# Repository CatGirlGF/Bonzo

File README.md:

# Bonzo
## Pro Micro based custom pseudo 40% keyboard inspired by [V4N4G0N](https://trashman.wiki/keyboards/v4n4g0n)

## Kicad libraries used:

https://github.com/AcheronProject/AlexandriaLibrary
https://github.com/keebio/Keebio-Parts.pretty
https://github.com/ai03-2725/MX_Alps_Hybrid/tree/master/MX_Only.pretty

## Gerbers

The provided gerbers have been created according to the specifications of JLCpcb. For plate the size is 275.3mm * 113.4mm

## Cases 

### Acryllic case

The case is designed to be cut out of 3mm acryllic and uses a 1.5mm switchplate.

I used 4mm female to female M2 standoffs from this listing: https://www.aliexpress.com/item/1005003106030065.html

https://i.imgur.com/W8KVRhH.png Picture for reference if the listing gets deleted

### 3D printable case WIP

This case has been printed fully and works, but the screwholes are too tight and have to be drilled.

Updated case design with heat insrets and correct size holes at some point.

## Firmware 

I have provided a compiled .hex and a layout json that will let you use the keyboard with VIA.

The full QMK library is also provided incase it is needed.

## BOM

### General parts for wired

| Name                    | Pieces | Description                          |
| ----------------------- | ------ | ------------------------------------ |
| PCB                     | 1      | Gerbers available at this repository |
| 1,5mm switch plate      | 1      | Gerbers available at this repository |
| 2U PCB mount stabilizer | 3      | Also known as screw-in stabilizers   |
| MX hotswap sockets      | 54     | Kailh or equivalent                  |
| MX style switch         | 54     |                                      |
| 1N4148 diodes           | 54     | SOD-123 packaging                    |
| ProMicro or similar     | 1      |                                      |

### For Wireless

| Name                    | Pieces | Description                                                                                            |
| ----------------------- | ------ | ------------------------------------------------------------------------------------------------------ |
| PCB                     | 1      | Gerbers available at this repository                                                                   |
| 1,5mm switch plate      | 1      | Gerbers available at this repository                                                                   |
| 2U PCB mount stabilizer | 3      |                                                                                                        |
| MX hotswap sockets      | 54     | Kailh or equivalent                                                                                    |
| MX style switch         | 54     |                                                                                                        |
| 1N4148 diodes           | 54     | SOD-123 packaging                                                                                      |
| nice!nano v2            | 1      |                                                                                                        |
| LiPo battery            | 1      | Refer to [nice!nano's documentation](https://nicekeyboards.com/docs/nice-nano/) on battery suggestions |
| Slide switch            | 1      | JS202011AQN or similar                                                                                 |

#### For acryllic case

| Name                               | Pieces    | Description                        |
| ---------------------------------- | --------- | ---------------------------------- |
| Acrylic layers                     | 1 of each | Files available in this repository |
| 4-6mm M2 female - female standoffs | 8         | Hexagon shaped ones won't fit      |
| M2 screws                          | 16        |                                    |

#### For 3DP case

| Name         | Pieces | Description                         |
| ------------ | ------ | ----------------------------------- |
| Top case     | 1      |                                     |
| Bottom case  | 1      |                                     |
| M2x15 screws | 4      | Self-tapping screws are recommended |
| M2x10 screws | 4      | Self-tapping screws are recommended |

## Keycaps
You will also need keycaps to fit the layout pictured below 

# Disclaimer
**Everything in this repo has been published with intent to allow others to build this keyboard if they want to and is published under MIT License. The versions I have uploaded have been tested to work. I take no responsibility of designs being incorrect or flawed. Check all the files yourself before you purchase anything. If something is broken or missing please let me know and ill try and see if I can fix the issue.**

Also here is the cat who inspired the name and the silkscreen

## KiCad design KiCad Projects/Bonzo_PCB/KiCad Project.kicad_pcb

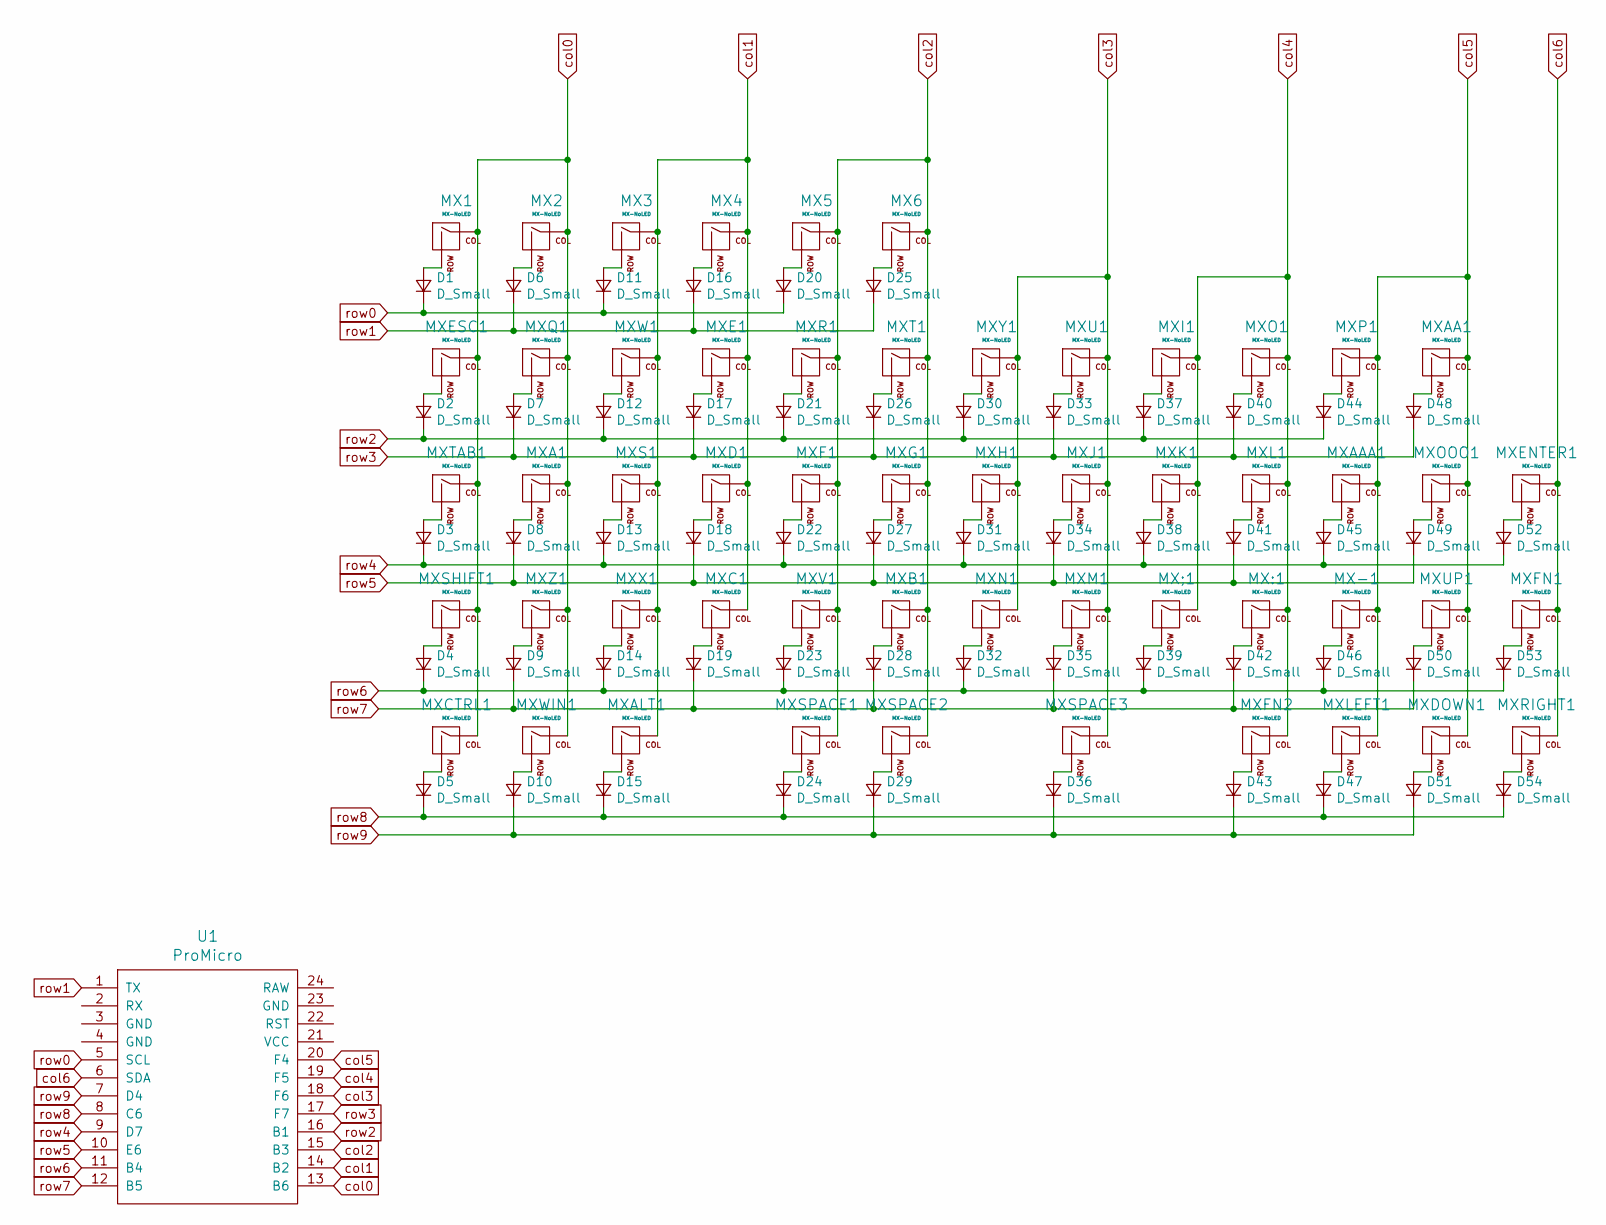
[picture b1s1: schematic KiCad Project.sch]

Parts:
D1, D2, D3, D4, D5, D6, D7, D8, D9, D10, D11, D12, D13, D14, D15, D16, D17, D18, D19, D20, D21, D22, D23, D24, D25, D26, D27, D28, D29, D30, D31, D32, D33, D34, D35, D36, D37, D38, D39, D40, D41, D42, D43, D44, D45, D46, D47, D48, D49, D50, D51, D52, D53, D54: D_Small; D_SOD123
MX1, MX2, MX3, MX4, MX5, MX6: MX-NoLED; MXOnly-1U-Hotswap
MX-1: MX-NoLED; MXOnly-1U-Hotswap
MX:1: MX-NoLED; MXOnly-1U-Hotswap
MX;1: MX-NoLED; MXOnly-1U-Hotswap
MXA1: MX-NoLED; MXOnly-1U-Hotswap
MXAA1: MX-NoLED; MXOnly-1U-Hotswap
MXAAA1: MX-NoLED; MXOnly-1U-Hotswap
MXALT1: MX-NoLED; MXOnly-1.25U-Hotswap
MXB1: MX-NoLED; MXOnly-1U-Hotswap
MXC1: MX-NoLED; MXOnly-1U-Hotswap
MXCTRL1: MX-NoLED; MXOnly-1.25U-Hotswap
MXD1: MX-NoLED; MXOnly-1U-Hotswap
MXDOWN1: MX-NoLED; MXOnly-1U-Hotswap
MXE1: MX-NoLED; MXOnly-1U-Hotswap
MXENTER1: MX-NoLED; MX_ISOEnter_VerticalH
MXESC1: MX-NoLED; MXOnly-1U-Hotswap
MXF1: MX-NoLED; MXOnly-1U-Hotswap
MXFN1, MXFN2: MX-NoLED; MXOnly-1U-Hotswap
MXG1: MX-NoLED; MXOnly-1U-Hotswap
MXH1: MX-NoLED; MXOnly-1U-Hotswap
MXI1: MX-NoLED; MXOnly-1U-Hotswap
MXJ1: MX-NoLED; MXOnly-1U-Hotswap
MXK1: MX-NoLED; MXOnly-1U-Hotswap
MXL1: MX-NoLED; MXOnly-1U-Hotswap
MXLEFT1: MX-NoLED; MXOnly-1U-Hotswap
MXM1: MX-NoLED; MXOnly-1U-Hotswap
MXN1: MX-NoLED; MXOnly-1U-Hotswap
MXO1: MX-NoLED; MXOnly-1U-Hotswap
MXOOO1: MX-NoLED; MXOnly-1U-Hotswap
MXP1: MX-NoLED; MXOnly-1U-Hotswap
MXQ1: MX-NoLED; MXOnly-1U-Hotswap
MXR1: MX-NoLED; MXOnly-1U-Hotswap
MXRIGHT1: MX-NoLED; MXOnly-1U-Hotswap
MXS1: MX-NoLED; MXOnly-1U-Hotswap
MXSHIFT1: MX-NoLED; MXOnly-1.5U-Hotswap
MXSPACE1: MX-NoLED; MXOnly-2.75U-Hotswap-ReversedStabilizers
MXSPACE2: MX-NoLED; MXOnly-1U-Hotswap
MXSPACE3: MX-NoLED; MXOnly-2.25U-Hotswap-ReversedStabilizers
MXT1: MX-NoLED; MXOnly-1U-Hotswap
MXTAB1: MX-NoLED; MXOnly-1.25U-Hotswap
MXU1: MX-NoLED; MXOnly-1U-Hotswap
MXUP1: MX-NoLED; MXOnly-1U-Hotswap
MXV1: MX-NoLED; MXOnly-1U-Hotswap
MXW1: MX-NoLED; MXOnly-1U-Hotswap
MXWIN1: MX-NoLED; MXOnly-1U-Hotswap
MXX1: MX-NoLED; MXOnly-1U-Hotswap
MXY1: MX-NoLED; MXOnly-1U-Hotswap
MXZ1: MX-NoLED; MXOnly-1U-Hotswap
U1: ProMicro; ArduinoProMicro

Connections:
unnamed: D1.2 (A), MX1.2 (ROW)
unnamed: D2.2 (A), MXESC1.2 (ROW)
unnamed: D3.2 (A), MXTAB1.2 (ROW)
unnamed: D4.2 (A), MXSHIFT1.2 (ROW)
unnamed: D5.2 (A), MXCTRL1.2 (ROW)
unnamed: D6.2 (A), MX2.2 (ROW)
unnamed: D7.2 (A), MXQ1.2 (ROW)
unnamed: D8.2 (A), MXA1.2 (ROW)
unnamed: D9.2 (A), MXZ1.2 (ROW)
unnamed: D10.2 (A), MXWIN1.2 (ROW)
unnamed: D11.2 (A), MX3.2 (ROW)
unnamed: D12.2 (A), MXW1.2 (ROW)
unnamed: D13.2 (A), MXS1.2 (ROW)
unnamed: D14.2 (A), MXX1.2 (ROW)
unnamed: D15.2 (A), MXALT1.2 (ROW)
unnamed: D16.2 (A), MX4.2 (ROW)
unnamed: D17.2 (A), MXE1.2 (ROW)
unnamed: D18.2 (A), MXD1.2 (ROW)
unnamed: D19.2 (A), MXC1.2 (ROW)
unnamed: D20.2 (A), MX5.2 (ROW)
unnamed: D21.2 (A), MXR1.2 (ROW)
unnamed: D22.2 (A), MXF1.2 (ROW)
unnamed: D23.2 (A), MXV1.2 (ROW)
unnamed: D24.2 (A), MXSPACE1.2 (ROW)
unnamed: D25.2 (A), MX6.2 (ROW)
unnamed: D26.2 (A), MXT1.2 (ROW)
unnamed: D27.2 (A), MXG1.2 (ROW)
unnamed: D28.2 (A), MXB1.2 (ROW)
unnamed: D29.2 (A), MXSPACE2.2 (ROW)
unnamed: D30.2 (A), MXY1.2 (ROW)
unnamed: D31.2 (A), MXH1.2 (ROW)
unnamed: D32.2 (A), MXN1.2 (ROW)
unnamed: D33.2 (A), MXU1.2 (ROW)
unnamed: D34.2 (A), MXJ1.2 (ROW)
unnamed: D35.2 (A), MXM1.2 (ROW)
unnamed: D36.2 (A), MXSPACE3.2 (ROW)
unnamed: D37.2 (A), MXI1.2 (ROW)
unnamed: D38.2 (A), MXK1.2 (ROW)
unnamed: D39.2 (A), MX;1.2 (ROW)
unnamed: D40.2 (A), MXO1.2 (ROW)
unnamed: D41.2 (A), MXL1.2 (ROW)
unnamed: D42.2 (A), MX:1.2 (ROW)
unnamed: D43.2 (A), MXFN2.2 (ROW)
unnamed: D44.2 (A), MXP1.2 (ROW)
unnamed: D45.2 (A), MXAAA1.2 (ROW)
unnamed: D46.2 (A), MX-1.2 (ROW)
unnamed: D47.2 (A), MXLEFT1.2 (ROW)
unnamed: D48.2 (A), MXAA1.2 (ROW)
unnamed: D49.2 (A), MXOOO1.2 (ROW)
unnamed: D50.2 (A), MXUP1.2 (ROW)
unnamed: D51.2 (A), MXDOWN1.2 (ROW)
unnamed: D52.2 (A), MXENTER1.2 (ROW)
unnamed: D53.2 (A), MXFN1.2 (ROW)
unnamed: D54.2 (A), MXRIGHT1.2 (ROW)
col0: MX1.1 (COL), MX2.1 (COL), MXA1.1 (COL), MXCTRL1.1 (COL), MXESC1.1 (COL), MXQ1.1 (COL), MXSHIFT1.1 (COL), MXTAB1.1 (COL), MXWIN1.1 (COL), MXZ1.1 (COL), U1.13 (B6)
col1: MX3.1 (COL), MX4.1 (COL), MXALT1.1 (COL), MXC1.1 (COL), MXD1.1 (COL), MXE1.1 (COL), MXS1.1 (COL), MXW1.1 (COL), MXX1.1 (COL), U1.14 (B2)
col2: MX5.1 (COL), MX6.1 (COL), MXB1.1 (COL), MXF1.1 (COL), MXG1.1 (COL), MXR1.1 (COL), MXSPACE1.1 (COL), MXSPACE2.1 (COL), MXT1.1 (COL), MXV1.1 (COL), U1.15 (B3)
col3: MXH1.1 (COL), MXJ1.1 (COL), MXM1.1 (COL), MXN1.1 (COL), MXSPACE3.1 (COL), MXU1.1 (COL), MXY1.1 (COL), U1.18 (F6)
col4: MX:1.1 (COL), MX;1.1 (COL), MXFN2.1 (COL), MXI1.1 (COL), MXK1.1 (COL), MXL1.1 (COL), MXO1.1 (COL), U1.19 (F5)
col5: MX-1.1 (COL), MXAA1.1 (COL), MXAAA1.1 (COL), MXDOWN1.1 (COL), MXLEFT1.1 (COL), MXOOO1.1 (COL), MXP1.1 (COL), MXUP1.1 (COL), U1.20 (F4)
col6: MXENTER1.1 (COL), MXFN1.1 (COL), MXRIGHT1.1 (COL), U1.6 (SDA)
row0: D1.1 (K), D11.1 (K), D20.1 (K), U1.5 (SCL)
row1: D6.1 (K), D16.1 (K), D25.1 (K), U1.1 (TX)
row2: D2.1 (K), D12.1 (K), D21.1 (K), D30.1 (K), D37.1 (K), D44.1 (K), U1.16 (B1)
row3: D7.1 (K), D17.1 (K), D26.1 (K), D33.1 (K), D40.1 (K), D48.1 (K), U1.17 (F7)
row4: D3.1 (K), D13.1 (K), D22.1 (K), D31.1 (K), D38.1 (K), D45.1 (K), D52.1 (K), U1.9 (D7)
row5: D8.1 (K), D18.1 (K), D27.1 (K), D34.1 (K), D41.1 (K), D49.1 (K), U1.10 (E6)
row6: D4.1 (K), D14.1 (K), D23.1 (K), D32.1 (K), D39.1 (K), D46.1 (K), D53.1 (K), U1.11 (B4)
row7: D9.1 (K), D19.1 (K), D28.1 (K), D35.1 (K), D42.1 (K), D50.1 (K), U1.12 (B5)
row8: D5.1 (K), D15.1 (K), D24.1 (K), D47.1 (K), D54.1 (K), U1.8 (C6)
row9: D10.1 (K), D29.1 (K), D36.1 (K), D43.1 (K), D51.1 (K), U1.7 (D4)

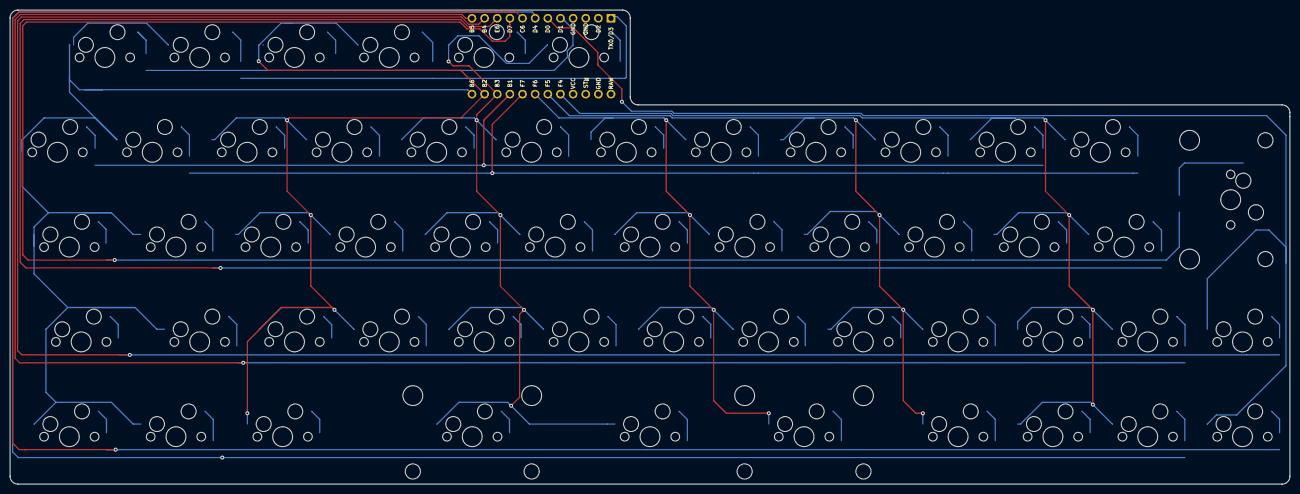
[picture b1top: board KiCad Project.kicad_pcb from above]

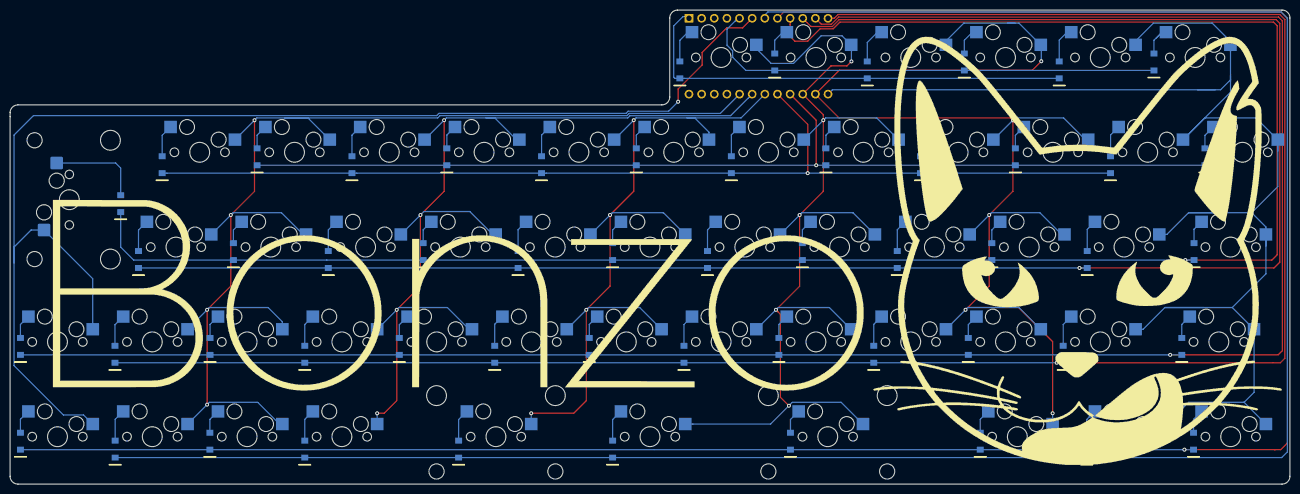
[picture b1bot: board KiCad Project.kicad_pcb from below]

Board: 2 copper layers, 257.2 x 95.2 mm, 109 parts (55 on the bottom side), 71 nets.

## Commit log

2022-05-14 Added a case with battery compartment
2022-05-18 Add ZMK board config + 3DP case files for wireless version.
2022-08-31 Fixed Markdown and added crucial information
